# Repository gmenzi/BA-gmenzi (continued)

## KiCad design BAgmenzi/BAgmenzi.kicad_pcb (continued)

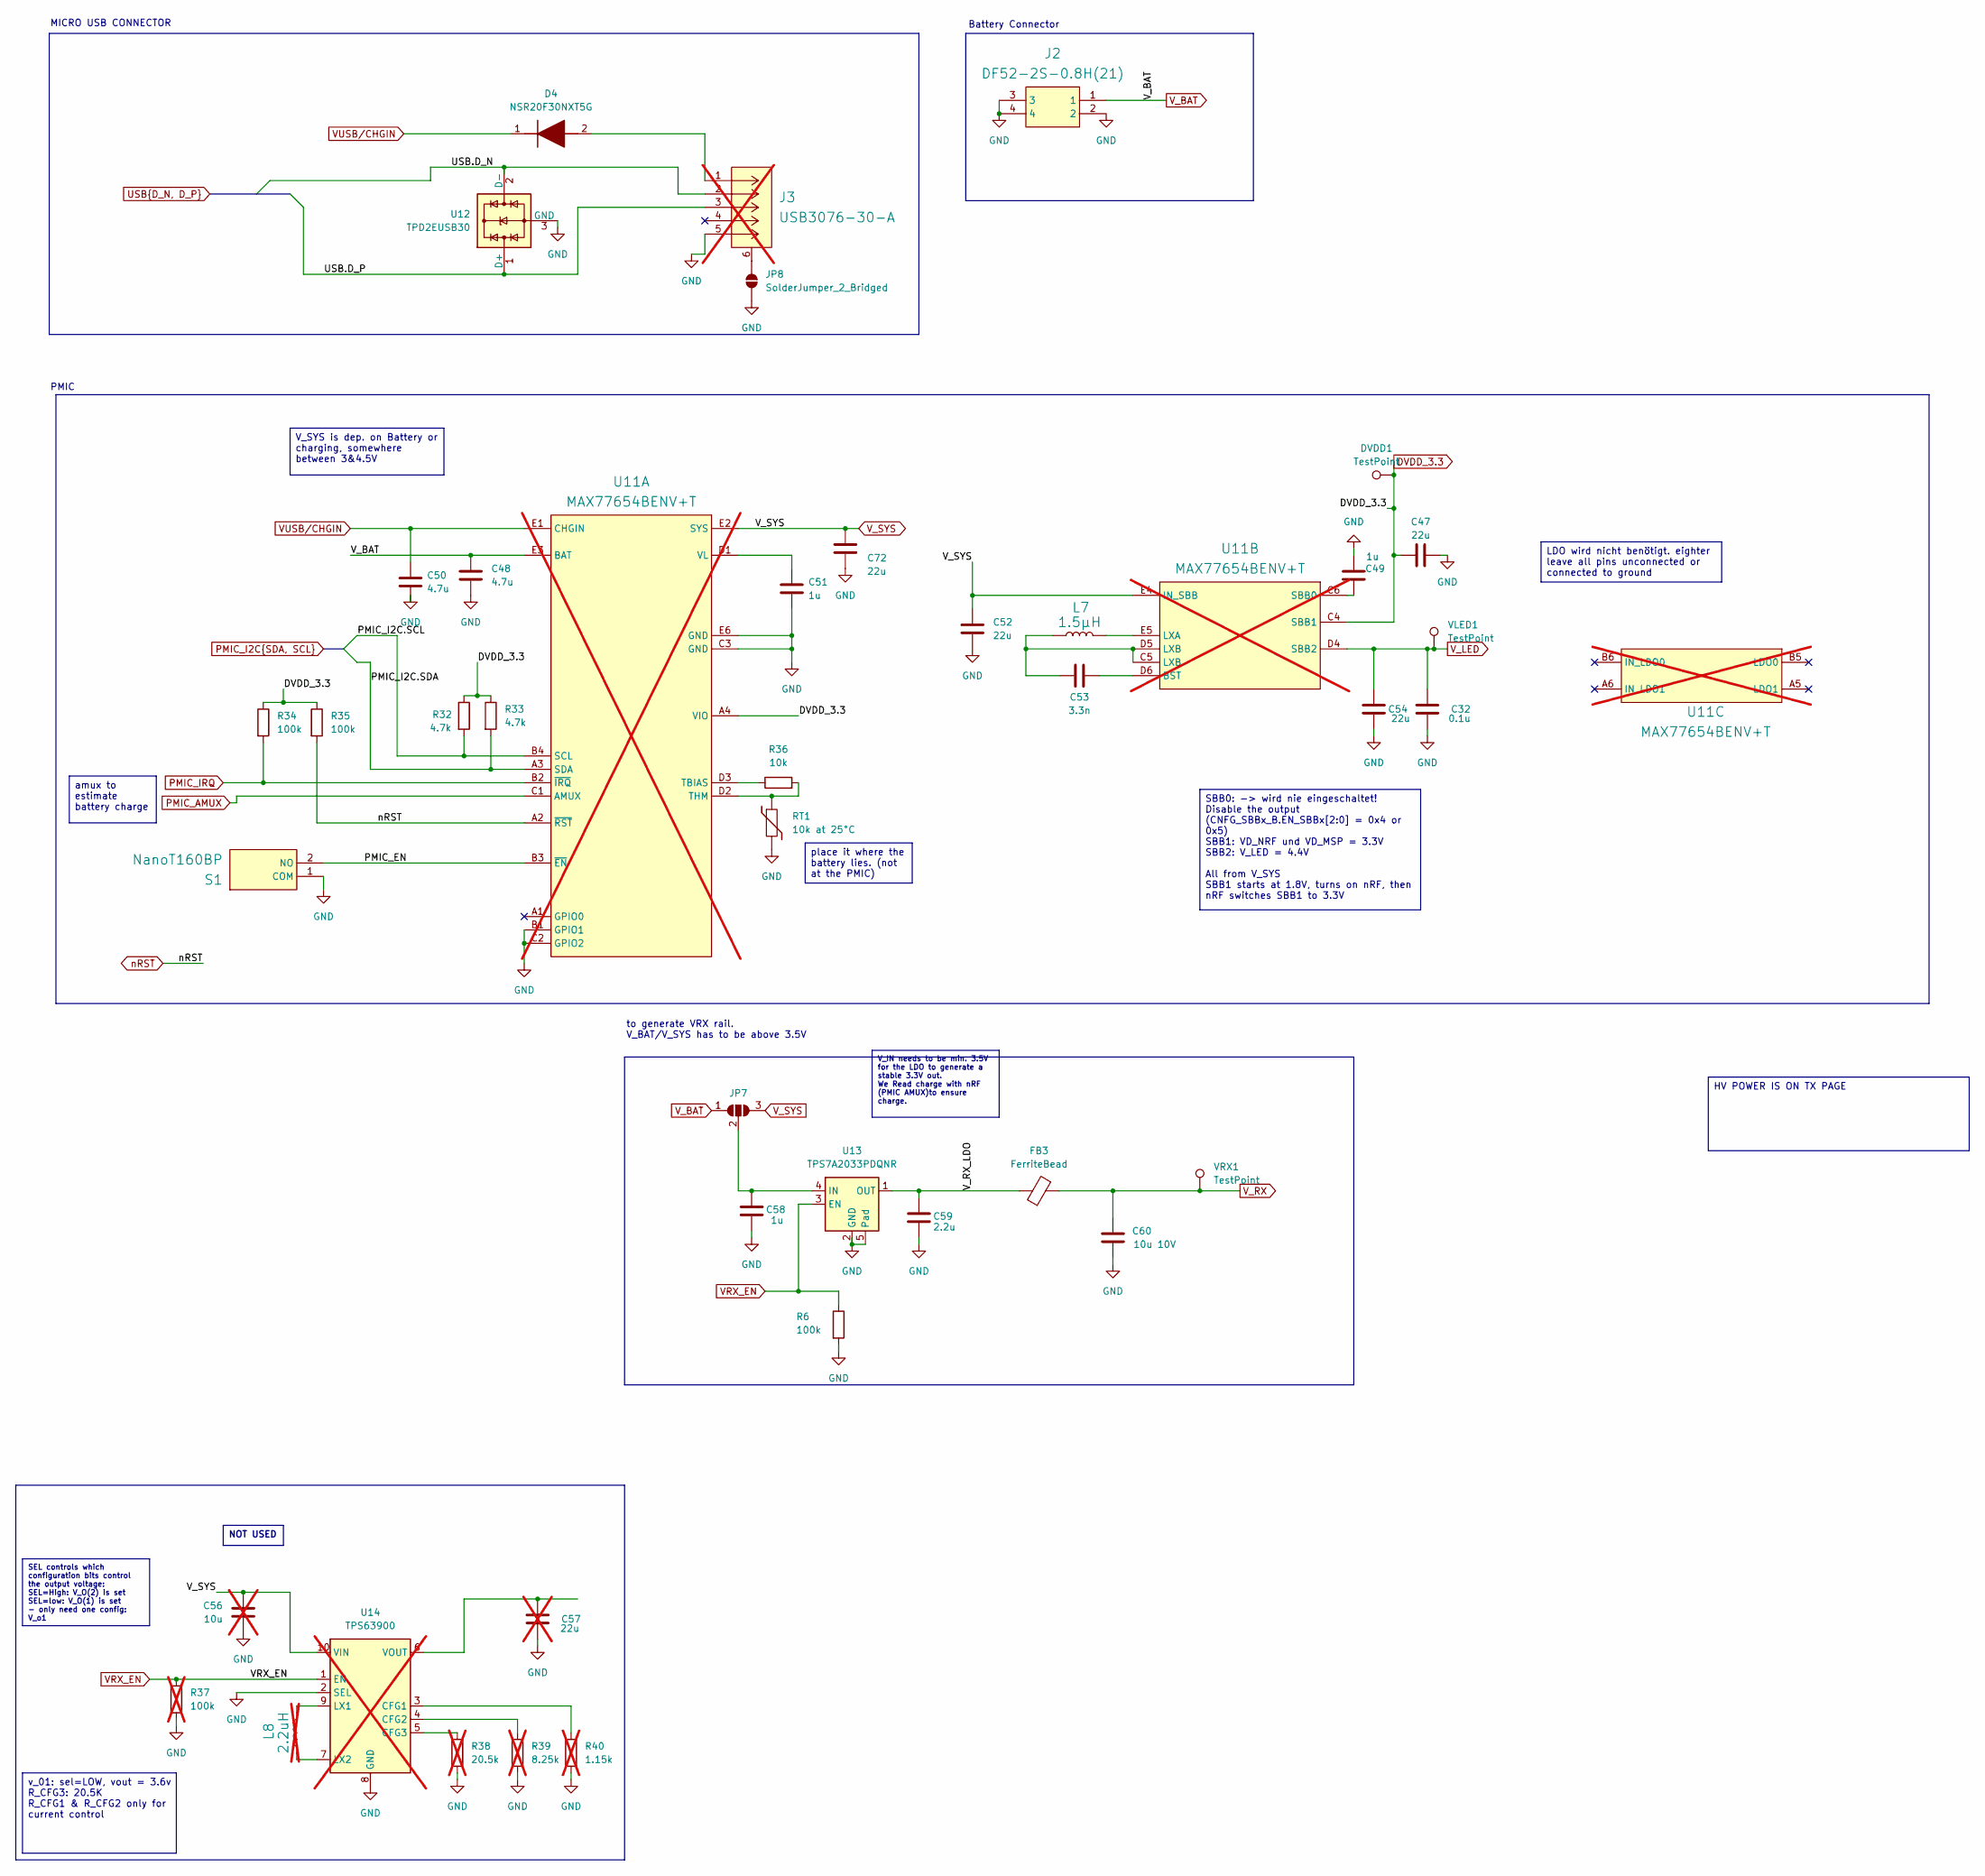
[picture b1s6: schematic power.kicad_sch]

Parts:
C32: 0.1u; C_0402_1005Metric; LCSC Part # C1525
C47, C52, C54, C72: 22u; C_0402_1005Metric; LCSC Part # C105226
C48, C50: 4.7u; C_0402_1005Metric; LCSC Part # C23733
C49, C51, C58: 1u; C_0402_1005Metric; LCSC Part # C14445
C53: 3.3n; C_0402_1005Metric; LCSC Part # C26404
C56: 10u; C_0402_1005Metric; not fitted
C57: 22u; C_0402_1005Metric; not fitted
C59: 2.2u; C_0402_1005Metric; LCSC Part # C77002
C60: 10u 10V; C_0402_1005Metric; LCSC Part # C408132
D4: NSR20F30NXT5G; DSN2_1; Manufacturer_Part_Number NSR20F30NXT5G; Mouser Part Number 863-NSR20F30NXT5G
DVDD1: TestPoint; TestPoint_Pad_D1.0mm
FB3: FerriteBead; L_0603_1608Metric; LCSC Part # C3717002
J2: DF52-2S-0.8H(21); DF522S08H21; Manufacturer_Part_Number DF52-2S-0.8H(21); Mouser Part Number 798-DF52-2S-0.8H21
J3: USB3076-30-A; CONN_USB3076-30-A_GCT; Manufacturer_Part_Number USB3076-30-A; LCSC Part # C6007475; not fitted
JP7: SolderJumper_3_Open; SolderJumper-3_P1.3mm_Open_Pad1.0x1.5mm
JP8: SolderJumper_2_Bridged; SolderJumper-2_P1.3mm_Open_Pad1.0x1.5mm
L7: 1.5µH; IND_0805_DFE201210S; Manufacturer Part Number DFE201210S-1R5M=P2; LCSC Part # C2891571
L8: 2.2uH; L_Murata_DFE201610P; Manufacturer Part Number DFE201210S-1R5M=P2; not fitted
R6, R34, R35: 100k; R_0402_1005Metric; LCSC Part # C192169
R32, R33: 4.7k; R_0402_1005Metric; LCSC Part # C25900
R36: 10k; R_0402_1005Metric; LCSC Part # C191984
R37: 100k; R_0402_1005Metric; not fitted
R38: 20.5k; R_0402_1005Metric; not fitted
R39: 8.25k; R_0402_1005Metric; not fitted
R40: 1.15k; R_0402_1005Metric; not fitted
RT1: 10k at 25°C; R_0402_1005Metric; LCSC Part # C77131
S1: NanoT160BP; Manufacturer_Part_Number NanoT160BP; LCSC Part # C2760983
U11: MAX77654BENV+T; WLP_30_MAX77654; Manufacturer Part Number MAX77654BENV+T; LCSC Part # C3189129; not fitted
U12: TPD2EUSB30; Texas_DRT-3; LCSC Part # C94934
U13: TPS7A2033PDQNR; Texas_X2SON-4_1x1mm_P0.65mm; LCSC Part # C2871641
U14: TPS63900; WSON-10-1EP_2.5x2.5mm_P0.5mm_EP1.2x2mm_ThermalVias; not fitted
VLED1: TestPoint; TestPoint_Pad_D1.0mm
VRX1: TestPoint; TestPoint_Pad_D1.0mm

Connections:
/POWER/PMIC_EN: S1.2 (NO), U11.B3 (~EN)
/POWER/V_RX_LDO: C59.1, FB3.1, U13.1 (OUT)
DVDD_3.3: C47.1, DVDD1.1, R32.1, R33.1, R34.1, R35.1, U11.A4 (VIO), U11.C4 (SBB1); also elsewhere on the board
GND: C32.2, C47.2, C48.2, C49.2, C50.2, C51.2, C52.2, C54.2, C56.2, C57.2, C58.2, C59.2, C60.2, C72.2, J2.2, J2.3, J2.4, J3.5, JP8.1 (A), R6.2, R37.1, R38.1, R39.1, R40.1, RT1.2, S1.1 (COM), U11.B1 (GPIO1), U11.C2 (GPIO2), U11.C3 (GND), U11.E6 (GND), U12.3 (GND), U13.2 (GND), U13.5 (Pad), U14.2 (SEL), U14.8 (GND), U14.11 (GND); also elsewhere on the board
unnamed: C53.1, L7.1, U11.C5 (LXB), U11.D5 (LXB)
unnamed: C57.1, U14.6 (VOUT)
unnamed: D4.2 (A), J3.1
unnamed: J3.6 (SHIELD), JP8.2 (B)
unnamed: C58.1, JP7.2 (C), U13.4 (IN)
unnamed: L8.1, U14.7 (LX2)
unnamed: L8.2, U14.9 (LX1)
unnamed: R38.2, U14.5 (CFG3)
unnamed: R39.2, U14.4 (CFG2)
unnamed: R40.2, U14.3 (CFG1)
unnamed: R36.1, U11.D3 (TBIAS)
unnamed: R36.2, RT1.1, U11.D2 (THM)
unnamed: C51.1, U11.D1 (VL)
unnamed: C53.2, U11.D6 (BST)
unnamed: L7.2, U11.E5 (LXA)
unnamed: C49.1, U11.C6 (SBB0)
PMIC_AMUX: U11.C1 (AMUX); also elsewhere on the board
PMIC_I2C.SCL: R32.2, U11.B4 (SCL); also elsewhere on the board
PMIC_I2C.SDA: R33.2, U11.A3 (SDA); also elsewhere on the board
PMIC_IRQ: R34.2, U11.B2 (~IRQ); also elsewhere on the board
USB.D_N: J3.2, U12.2 (D-); also elsewhere on the board
USB.D_P: J3.3, U12.1 (D+); also elsewhere on the board
VRX_EN: R6.1, R37.2, U13.3 (EN), U14.1 (EN); also elsewhere on the board
VUSB/CHGIN: C50.1, D4.1 (K), U11.E1 (CHGIN); also elsewhere on the board
V_BAT: C48.1, J2.1, JP7.1 (A), U11.E3 (BAT); also elsewhere on the board
V_LED: C32.1, C54.1, U11.D4 (SBB2), VLED1.1; also elsewhere on the board
V_RX: C60.1, FB3.2, VRX1.1; also elsewhere on the board
V_SYS: C52.1, C56.1, C72.1, JP7.3 (B), U11.E2 (SYS), U11.E4 (IN_SBB), U14.10 (VIN); also elsewhere on the board
nRST: R35.2, U11.A2 (~RST); also elsewhere on the board

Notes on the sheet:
to generate VRX rail. V_BAT/V_SYS has to be above 3.5V
PMIC
MICRO USB CONNECTOR
Battery Connector
place it where the battery lies. (not at the PMIC)
SBB0: -> wird nie eingeschaltet! Disable the output (CNFG_SBBx_B.EN_SBBx[2:0] = 0x4 or 0x5) SBB1: VD_NRF und VD_MSP = 3.3V SBB2: V_LED = 4.4V All from V_SYS SBB1 starts at 1.8V, turns on nRF, then nRF switches SBB1 to 3.3V
HV POWER IS ON TX PAGE
amux to estimate battery charge
V_IN needs to be min. 3.5V for the LDO to generate a stable 3.3V out. We Read charge with nRF (PMIC AMUX)to ensure charge.
LDO wird nicht benötigt. eighter leave all pins unconnected or connected to ground
V_SYS is dep. on Battery or charging, somewhere between 3&4.5V
NOT USED
v_01: sel=LOW, vout = 3.6v R_CFG3: 20.5K R_CFG1 & R_CFG2 only for current control
SEL controls which configuration bits control the output voltage: SEL=High: V_O(2) is set SEL=low: V_O(1) is set - only need one config: V_o1

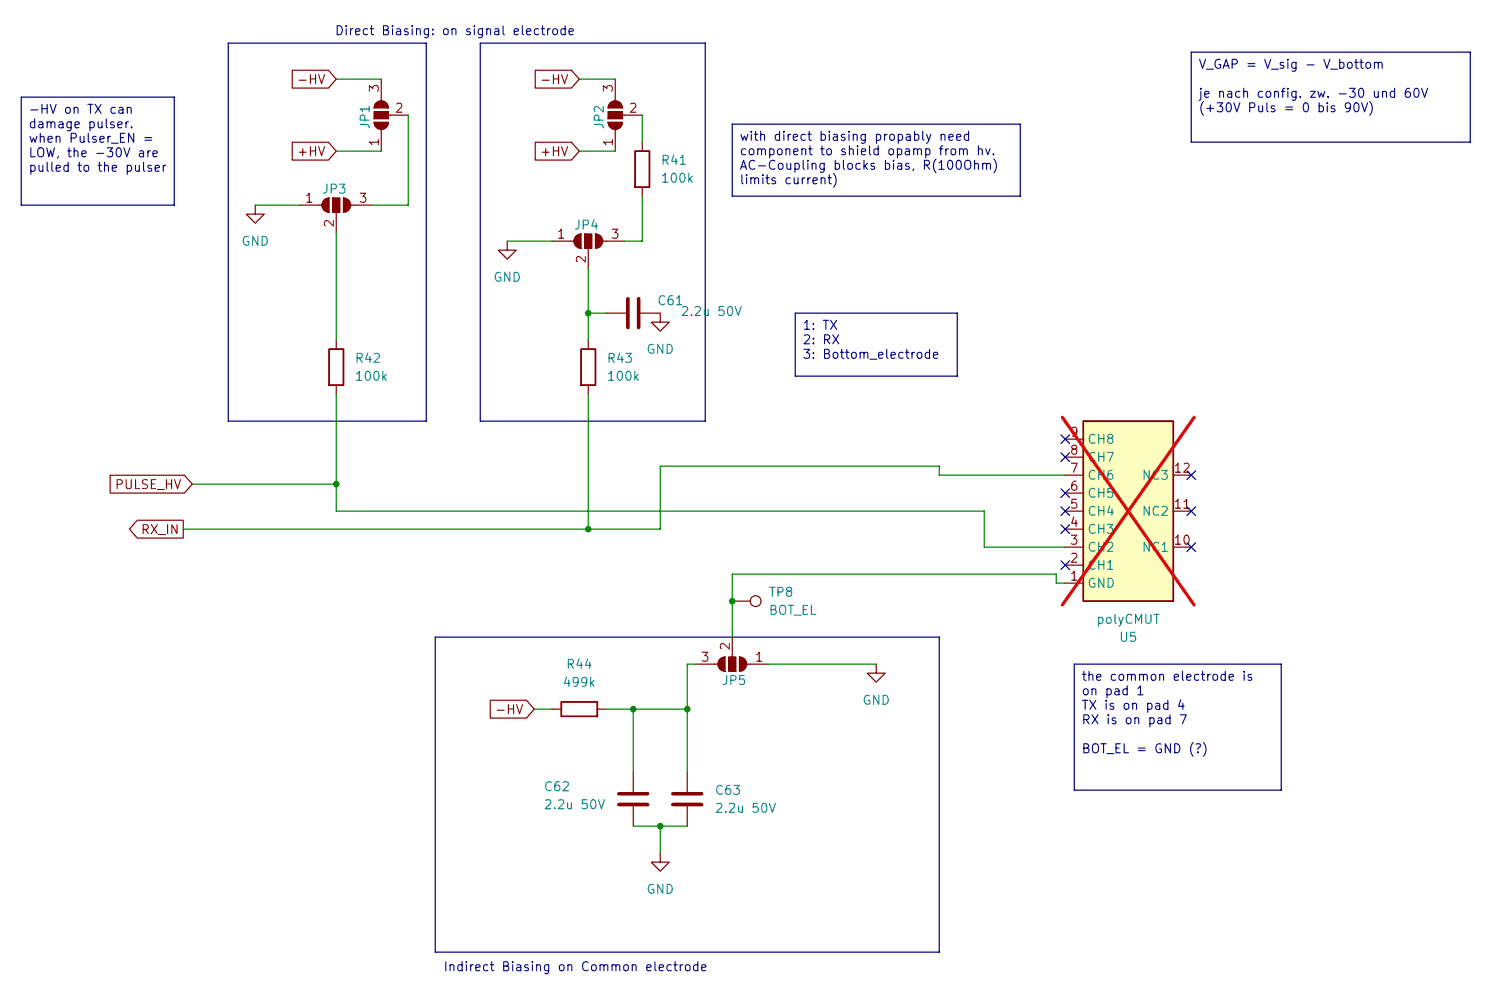
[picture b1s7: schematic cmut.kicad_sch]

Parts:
C61, C62, C63: 2.2u 50V; C_0603_1608Metric; LCSC Part # C668357
JP1, JP2, JP3, JP4, JP5: SolderJumper_3_Open; SolderJumper-3_P1.3mm_Open_Pad1.0x1.5mm
R41, R42: 100k; R_0402_1005Metric; LCSC Part # C192169
R43: 100k; 0402; LCSC Part # C192169
R44: 499k; 0402; LCSC Part # C25793
TP8: BOT_EL; TestPoint_Pad_D1.0mm
U5: polyCMUT; not fitted

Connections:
+HV: JP1.1 (A), JP2.1 (A); also elsewhere on the board
-HV: JP1.3 (B), JP2.3 (B), R44.1; also elsewhere on the board
GND: C61.1, C62.2, C63.2, JP3.1 (A), JP4.1 (A), JP5.1 (A); also elsewhere on the board
unnamed: JP1.2 (C), JP3.3 (B)
unnamed: JP2.2 (C), R41.1
unnamed: JP3.2 (C), R42.1
unnamed: JP4.3 (B), R41.2
unnamed: C61.2, JP4.2 (C), R43.1
unnamed: C62.1, C63.1, JP5.3 (B), R44.2
unnamed: JP5.2 (C), TP8.1, U5.1 (GND)
PULSE_HV: R42.2, U5.3 (CH2); also elsewhere on the board
RX_IN: R43.2, U5.7 (CH6); also elsewhere on the board

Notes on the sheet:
Indirect Biasing on Common electrode
Direct Biasing: on signal electrode
V_GAP = V_sig - V_bottom je nach config. zw. -30 und 60V (+30V Puls = 0 bis 90V)
with direct biasing propably need component to shield opamp from hv. AC-Coupling blocks bias, R(100Ohm) limits current)
the common electrode is on pad 1 TX is on pad 4 RX is on pad 7 BOT_EL = GND (?)
1: TX 2: RX 3: Bottom_electrode
-HV on TX can damage pulser. when Pulser_EN = LOW, the -30V are pulled to the pulser

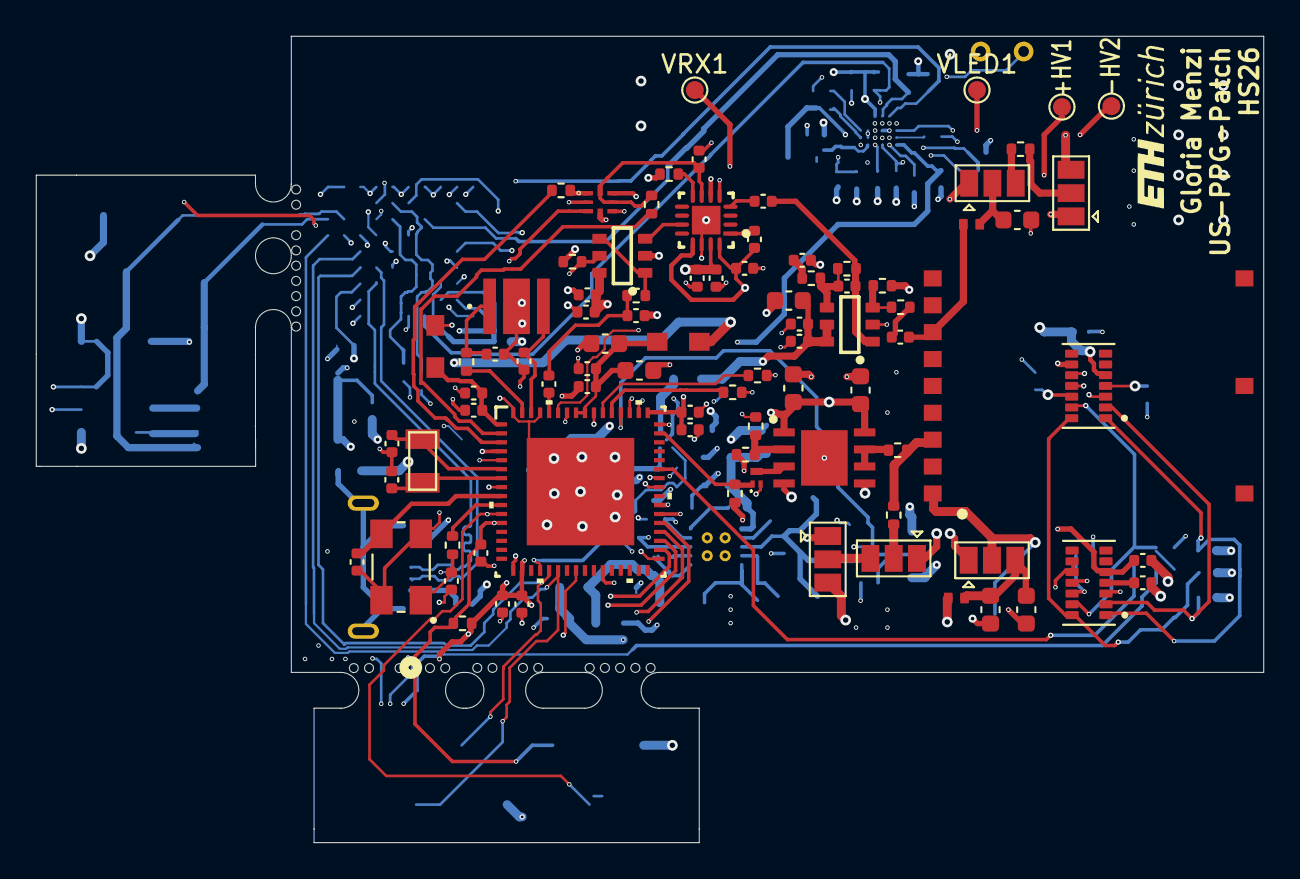
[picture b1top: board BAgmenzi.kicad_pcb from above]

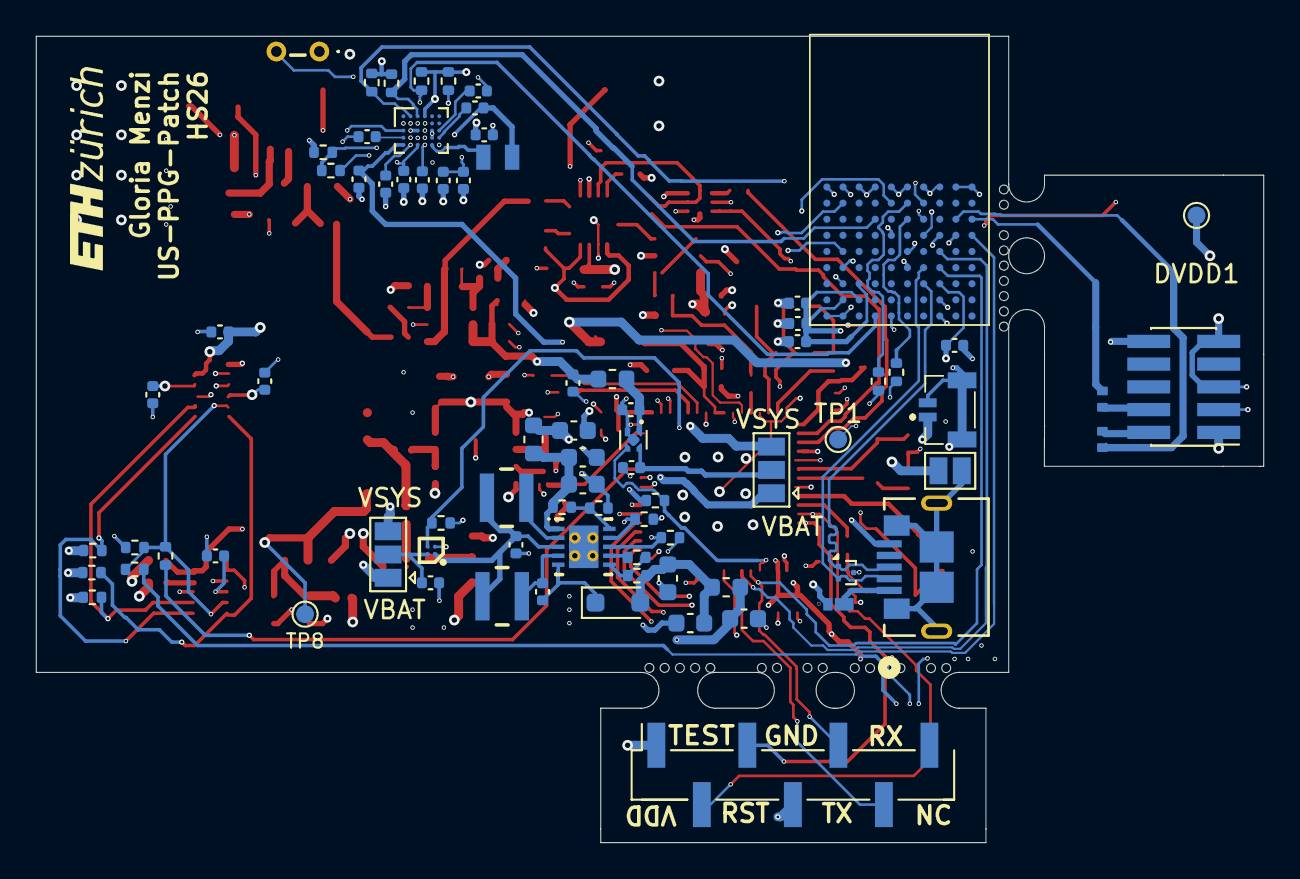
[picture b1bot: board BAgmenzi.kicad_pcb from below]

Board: 6 copper layers, 68.5 x 45.0 mm, 165 parts (79 on the bottom side), 117 nets.

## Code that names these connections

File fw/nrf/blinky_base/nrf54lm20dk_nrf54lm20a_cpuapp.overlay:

/*
 * Own-board signals on the nRF54LM20 DK.
 * P2 has no GPIOTE, so interrupt inputs must stay on P0, P1 or P3.
 */

/ {
	/* M7: PPG_NEW_APPL.C USES DEVICE_DT_GET(DT_ALIAS(I2CB)), AS IN BIOGAP. */
	aliases {
		i2cb = &i2c21;
		/* M8: PMIC_BSP.C AND PWR.C USE DEVICE_DT_GET(DT_ALIAS(I2CA)), AS IN
		 * SENSEI-SDK. DK: THE PPG BUS, BECAUSE THE OWN-BOARD PMIC PINS
		 * P0.07/P0.08 ARE THE DK'S UART30 (VCOM), DRIVEN BY THE DEBUGGER CHIP.
		 * THE DK HAS NO MAX77654, SO ADDRESS 0x48 SIMPLY GETS NO ACK.
		 * OWN BOARD: I2CA = &I2C30, SCL P0.07, SDA P0.08 (R32/R33 4.7K). */
		i2ca = &i2c21;
	};

	/* M8: PMIC_BSP.C READS ADC CHANNEL 0 OF ZEPHYR,USER FOR THE PMIC'S AMUX OUTPUT. */
	zephyr,user {
		io-channels = <&adc 0>;
	};

	patch_outputs {
		compatible = "gpio-leds";

		link_ready: link_ready {
			gpios = <&gpio2 6 GPIO_ACTIVE_HIGH>;
			label = "LINK_READY to MSP P5.7";
		};

		uups_trig: uups_trig {
			gpios = <&gpio1 11 GPIO_ACTIVE_HIGH>;
			label = "UUPS_TRIG_IN to MSP P1.7";
		};

		ppg_sync: ppg_sync {
			gpios = <&gpio1 12 GPIO_ACTIVE_LOW>;
			label = "PPG_GPIO sync";
		};

		/* M7: BIOGAP'S PPG_DEBUG TOGGLE OUTPUT. ON THE DK IT GOES TO LED2
		 * (P1.27), SO IT BLINKS EVERY 100 PPG SAMPLES. THE OWN BOARD HAS
		 * NO SUCH PIN: USE A SPARE PIN OR TEST POINT THERE. */
		ppg_debug: ppg_debug {
			gpios = <&gpio1 27 GPIO_ACTIVE_HIGH>;
			label = "PPG debug toggle (DK LED2)";
		};
	};

	patch_inputs {
		compatible = "gpio-leds";

		data_ready: data_ready {
			gpios = <&gpio1 10 (GPIO_ACTIVE_HIGH | GPIO_PULL_DOWN)>;
			label = "DATA_READY from MSP P6.0";
		};

		/* M7: LABEL RENAMED FROM PPG_INT TO PPG_INTB, THE NAME BIOGAP'S
		 * PPG_NEW_APPL.C EXPECTS. SAME PIN AS BEFORE. */
		ppg_intb: ppg_intb {
			gpios = <&gpio1 9 (GPIO_ACTIVE_LOW | GPIO_PULL_UP)>;
			label = "PPG_INT, BUTTON1 on the DK";
		};

		pmic_irq: pmic_irq {
			gpios = <&gpio0 5 (GPIO_ACTIVE_LOW | GPIO_PULL_UP)>;
			label = "PMIC_IRQ, BUTTON3 on the DK";
		};
	};
};

/* Creates a virtual serial port on the nRF's USB connector. */
&zephyr_udc0 {
	cdc_acm_uart0: cdc_acm_uart0 {
		compatible = "zephyr,cdc-acm-uart";
		label = "Patch data link";
	};
};

/*
 * DK only: the onboard flash shares SPI00 and uses P2.05 as CS.
 * Remove the flash node, keep P2.05 high, and use P1.13 as CS.
 * On the own board: remove the &gpio2 block and use P2.05 as CS.
 * WICHTIG: auf DK funktioniert port 2 nicht für SPI (MISO, MOSI) das fürs eigene board aber wieder zurücksetzen. -> &spi00
 */
/delete-node/ &mx25r64;

&gpio2 {
	dk_flash_cs_idle {
		gpio-hog;
		gpios = <5 GPIO_ACTIVE_HIGH>;
		output-high;
	};
};

&spi22 {
	status = "okay";
	cs-gpios = <&gpio1 13 GPIO_ACTIVE_LOW>;

	msp430: msp430@0 {
		compatible = "vnd,spi-device";
		reg = <0>;
		spi-max-frequency = <DT_FREQ_M(8)>;
	};
};

/*
 * M7: I2C TO THE MAXM86161.
 * DK: TWIM21 ON P1.07 (SCL) AND P1.06 (SDA), BOTH ON THE DK'S PIN HEADER.
 *  - NOT TWIM20: IT SHARES ITS HARDWARE WITH UART20, THE DK'S LOG CONSOLE.
 *  - NOT TWIM22: IT SHARES ITS HARDWARE WITH SPI22, USED FOR THE MSP ABOVE.
 *  - NOT P1.28 FOR SDA (OWN-BOARD PIN): ON THE DK IT DRIVES LED3.
 * OWN BOARD: SCL P1.07, SDA P1.28 (SEE PINBELEGUNG_MSP_NRF.XLSX).
 * BIAS-PULL-UP TURNS ON THE NRF'S WEAK INTERNAL PULL-UPS. THEY ARE ONLY A
 * FALLBACK: THE PPG BOARD SHOULD HAVE ITS OWN PULL-UP RESISTORS.
 */
&pinctrl {
	i2c21_default: i2c21_default {
		group1 {
			psels = <NRF_PSEL(TWIM_SCL, 1, 7)>,
				<NRF_PSEL(TWIM_SDA, 1, 6)>;
			bias-pull-up;
		};
	};

	i2c21_sleep: i2c21_sleep {
		group1 {
			psels = <NRF_PSEL(TWIM_SCL, 1, 7)>,
				<NRF_PSEL(TWIM_SDA, 1, 6)>;
			low-power-enable;
		};
	};
};

&i2c21 {
	status = "okay";
	pinctrl-0 = <&i2c21_default>;
	pinctrl-1 = <&i2c21_sleep>;
	pinctrl-names = "default", "sleep";
	/* M7: 400 KHZ. THE MAXM86161 SUPPORTS FAST MODE. but only with pullups. The PPG-Board has no pullups. */
	clock-frequency = <I2C_BITRATE_STANDARD>;
};

/*
 * M8: ADC FOR PMIC_AMUX ON P1.05 (SAME PIN ON THE DK HEADER AND THE OWN BOARD).
 * THE MAX77654 AMUX OUTPUT IS 0-1.25 V. INTERNAL REFERENCE 0.9 V WITH GAIN 1/2
 * GIVES 1.8 V FULL SCALE. PMIC_BSP.C TAKES VREF-MV AS THE FULL SCALE, SO IT IS
 * SET TO 1800 HERE (SENSEI: GAIN 1/6, 3600).
 * AIN5 = P1.05: FROM THE PATTERN IN NCS'S ADC SAMPLE FOR THIS DK (AIN4 = P1.06,
 * AIN6 = P1.04). CHECK IN THE NRF54LM20A PIN TABLE BEFORE TRUSTING THE VALUES.
 */
&adc {
	#address-cells = <1>;
	#size-cells = <0>;
	status = "okay";

	channel@0 {
		reg = <0>;
		zephyr,gain = "ADC_GAIN_1_2";
		zephyr,reference = "ADC_REF_INTERNAL";
		zephyr,vref-mv = <1800>;
		zephyr,acquisition-time = <ADC_ACQ_TIME_DEFAULT>;
		zephyr,input-positive = <NRF_SAADC_AIN5>; /* P1.05 */
		zephyr,resolution = <12>;
	};
};
